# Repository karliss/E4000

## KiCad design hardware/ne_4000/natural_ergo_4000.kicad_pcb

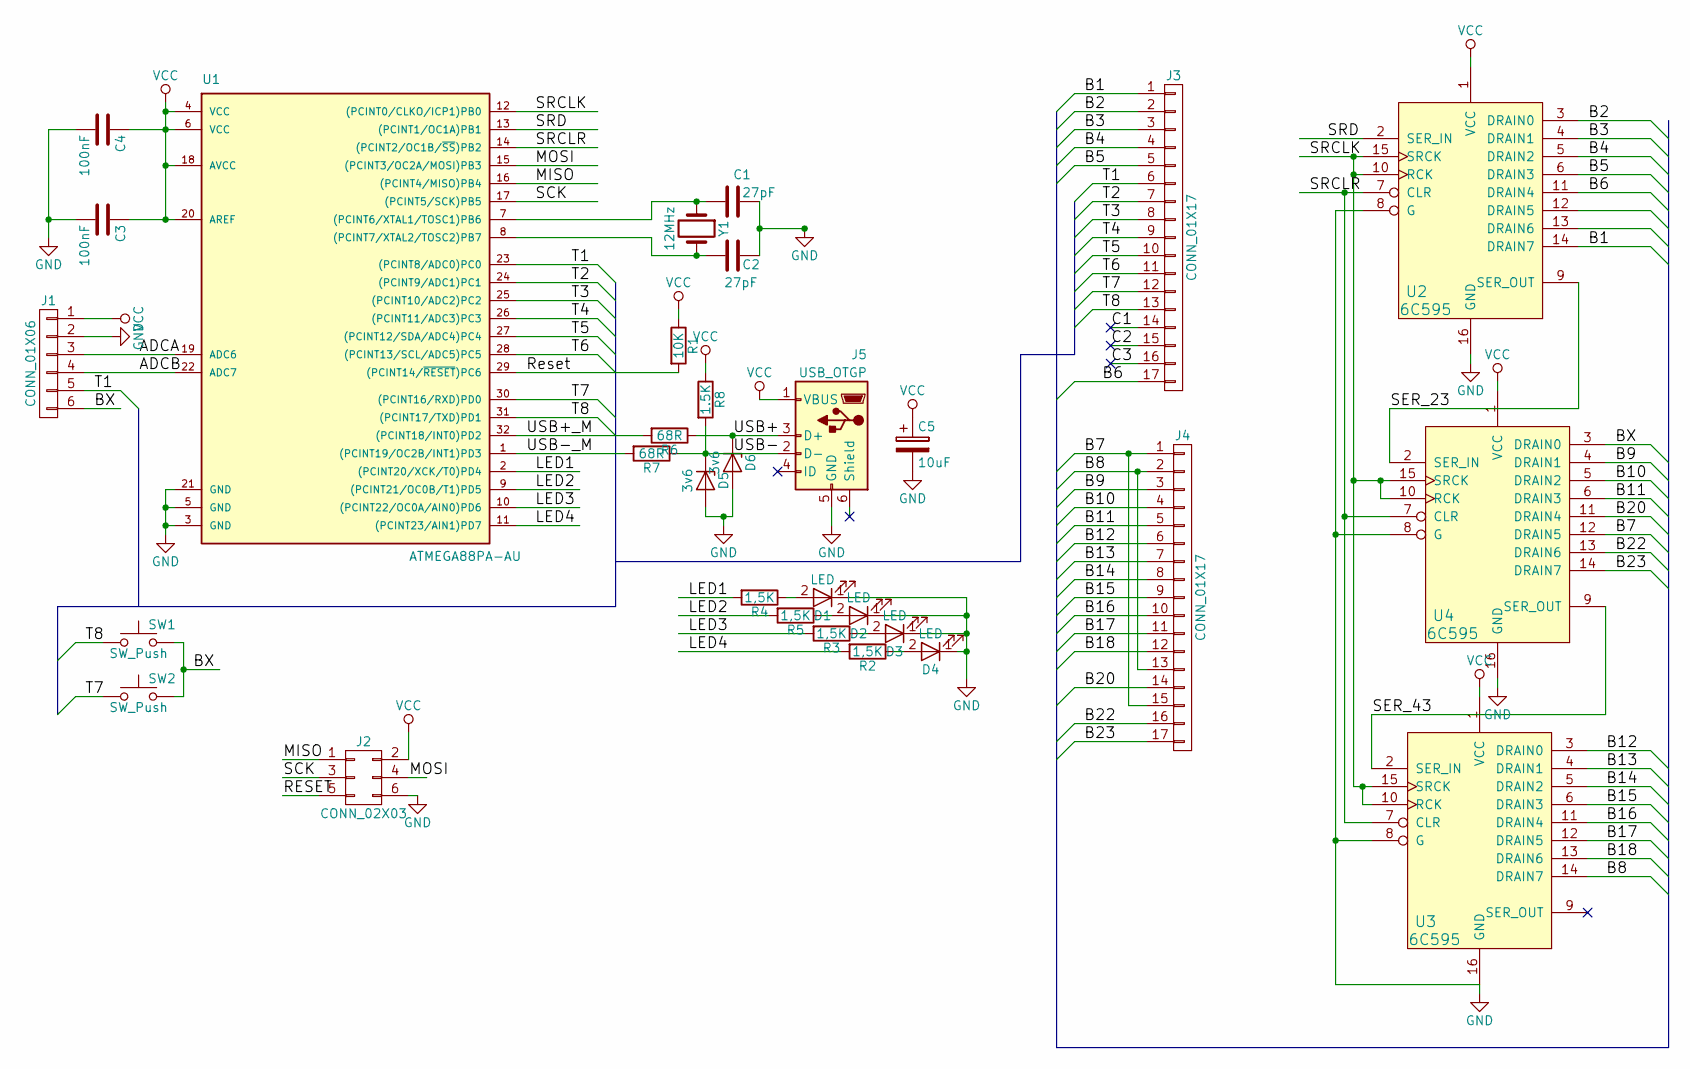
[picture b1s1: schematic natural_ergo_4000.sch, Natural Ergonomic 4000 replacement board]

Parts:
C1, C2: 27pF; C_Disc_D5.0mm_W2.5mm_P5.00mm
C3, C4: 100nF; C_0805
C5: 10uF; CP_Radial_D5.0mm_P2.50mm
D1, D2, D3, D4: LED; LED_D3.0mm
D5, D6: 3v6; D_DO-35_SOD27_P7.62mm_Horizontal
J1: CONN_01X06; Pin_Header_Straight_1x06_Pitch2.54mm
J2: CONN_02X03; Pin_Header_Straight_2x03_Pitch2.54mm
J3, J4: CONN_01X17; test_pad
J5: USB_OTGP; USB_Mini-B
R1: 10K; R_0805_HandSoldering
R2, R3, R4, R5: 1,5K; R_0805_HandSoldering
R6, R7: 68R; R_0805_HandSoldering
R8: 1.5K; R_0805_HandSoldering
SW1, SW2: SW_Push; SW_PUSH_6mm
U1: ATMEGA88PA-AU; LQFP-32_7x7mm_Pitch0.8mm
U2, U3, U4: 6C595; SOIC-16_3.9x9.9mm_Pitch1.27mm
Y1: 12MHz; Crystal_HC49-4H_Vertical

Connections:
/ADCA: J1.3, U1.19 (ADC6)
/ADCB: J1.4, U1.22 (ADC7)
/B1: J3.1, U2.14 (DRAIN7)
/B2: J3.2, U2.3 (DRAIN0)
/B3: J3.3, U2.4 (DRAIN1)
/B4: J3.4, U2.5 (DRAIN2)
/B5: J3.5, U2.6 (DRAIN3)
/B6: J3.17, U2.11 (DRAIN4)
/B7: J4.1, J4.15, U4.12 (DRAIN5)
/B8: J4.2, J4.13, U3.14 (DRAIN7)
/B9: J4.3, U4.4 (DRAIN1)
/B10: J4.4, U4.5 (DRAIN2)
/B11: J4.5, U4.6 (DRAIN3)
/B12: J4.6, U3.3 (DRAIN0)
/B13: J4.7, U3.4 (DRAIN1)
/B14: J4.8, U3.5 (DRAIN2)
/B15: J4.9, U3.6 (DRAIN3)
/B16: J4.10, U3.11 (DRAIN4)
/B17: J4.11, U3.12 (DRAIN5)
/B18: J4.12, U3.13 (DRAIN6)
/B20: J4.14, U4.11 (DRAIN4)
/B22: J4.16, U4.13 (DRAIN6)
/B23: J4.17, U4.14 (DRAIN7)
/BX: J1.6, SW1.2, SW2.2, U4.3 (DRAIN0)
/C1: J3.14
/C2: J3.15
/C3: J3.16
/LED1: R4.2, U1.2 ((PCINT20/XCK/T0)PD4)
/LED2: R5.2, U1.9 ((PCINT21/OC0B/T1)PD5)
/LED3: R3.2, U1.10 ((PCINT22/OC0A/AIN0)PD6)
/LED4: R2.2, U1.11 ((PCINT23/AIN1)PD7)
/MISO: J2.1, U1.16 ((PCINT4/MISO)PB4)
/MOSI: J2.4, U1.15 ((PCINT3/OC2A/MOSI)PB3)
/RESET: J2.5, R1.2, U1.29 ((PCINT14/~RESET~)PC6)
/SCK: J2.3, U1.17 ((PCINT5/SCK)PB5)
/SER_23: U2.9 (SER_OUT), U4.2 (SER_IN)
/SER_43: U3.2 (SER_IN), U4.9 (SER_OUT)
/SRCLK: U1.12 ((PCINT0/CLKO/ICP1)PB0), U2.10 (RCK), U2.15 (SRCK), U3.10 (RCK), U3.15 (SRCK), U4.10 (RCK), U4.15 (SRCK)
/SRCLR: U1.14 ((PCINT2/OC1B/~SS~)PB2), U2.7 (CLR), U3.7 (CLR), U4.7 (CLR)
/SRD: U1.13 ((PCINT1/OC1A)PB1), U2.2 (SER_IN)
/T1: J1.5, J3.6, U1.23 ((PCINT8/ADC0)PC0)
/T2: J3.7, U1.24 ((PCINT9/ADC1)PC1)
/T3: J3.8, U1.25 ((PCINT10/ADC2)PC2)
/T4: J3.9, U1.26 ((PCINT11/ADC3)PC3)
/T5: J3.10, U1.27 ((PCINT12/SDA/ADC4)PC4)
/T6: J3.11, U1.28 ((PCINT13/SCL/ADC5)PC5)
/T7: J3.12, SW2.1, U1.30 ((PCINT16/RXD)PD0)
/T8: J3.13, SW1.1, U1.31 ((PCINT17/TXD)PD1)
/USB+: D6.1 (K), J5.3 (D+), R6.1
/USB+_M: R6.2, U1.32 ((PCINT18/INT0)PD2)
/USB-: D5.1 (K), J5.2 (D-), R7.1, R8.2
/USB-_M: R7.2, U1.1 ((PCINT19/OC2B/INT1)PD3)
GND: C1.1, C2.1, C3.2, C4.2, C5.2, D1.1 (K), D2.1 (K), D3.1 (K), D4.1 (K), D5.2 (A), D6.2 (A), J1.2, J2.6, J5.5 (GND), U1.3 (GND), U1.5 (GND), U1.21 (GND), U2.8 (G), U2.16 (GND), U3.8 (G), U3.16 (GND), U4.8 (G), U4.16 (GND)
unnamed: C1.2, U1.7 ((PCINT6/XTAL1/TOSC1)PB6), Y1.1
unnamed: C2.2, U1.8 ((PCINT7/XTAL2/TOSC2)PB7), Y1.2
unnamed: D1.2 (A), R4.1
unnamed: D2.2 (A), R5.1
unnamed: D3.2 (A), R3.1
unnamed: D4.2 (A), R2.1
VCC: C3.1, C4.1, C5.1, J1.1, J2.2, J5.1 (VBUS), R1.1, R8.1, U1.4 (VCC), U1.6 (VCC), U1.18 (AVCC), U1.20 (AREF), U2.1 (VCC), U3.1 (VCC), U4.1 (VCC)

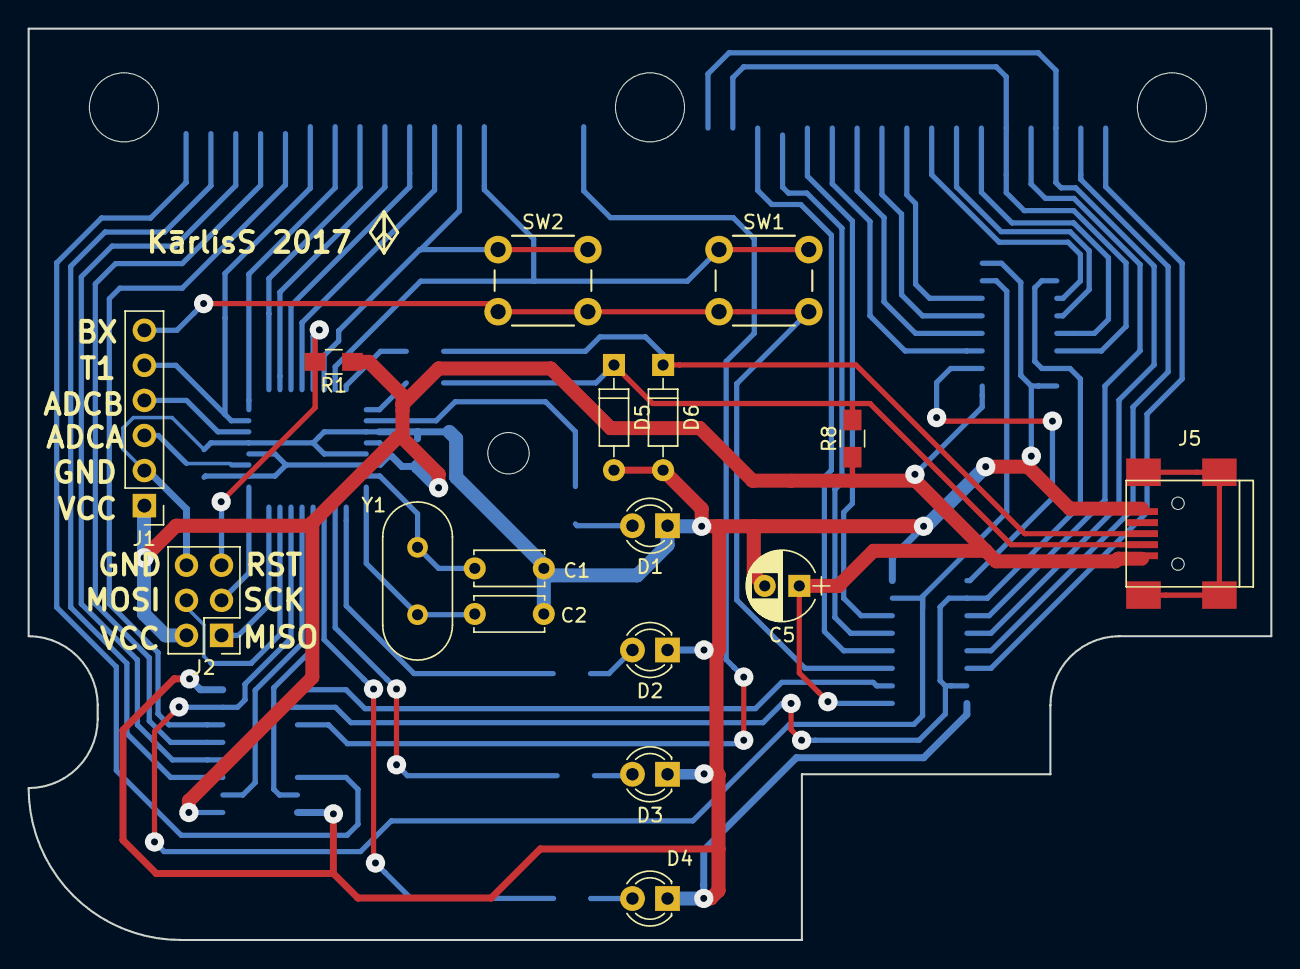
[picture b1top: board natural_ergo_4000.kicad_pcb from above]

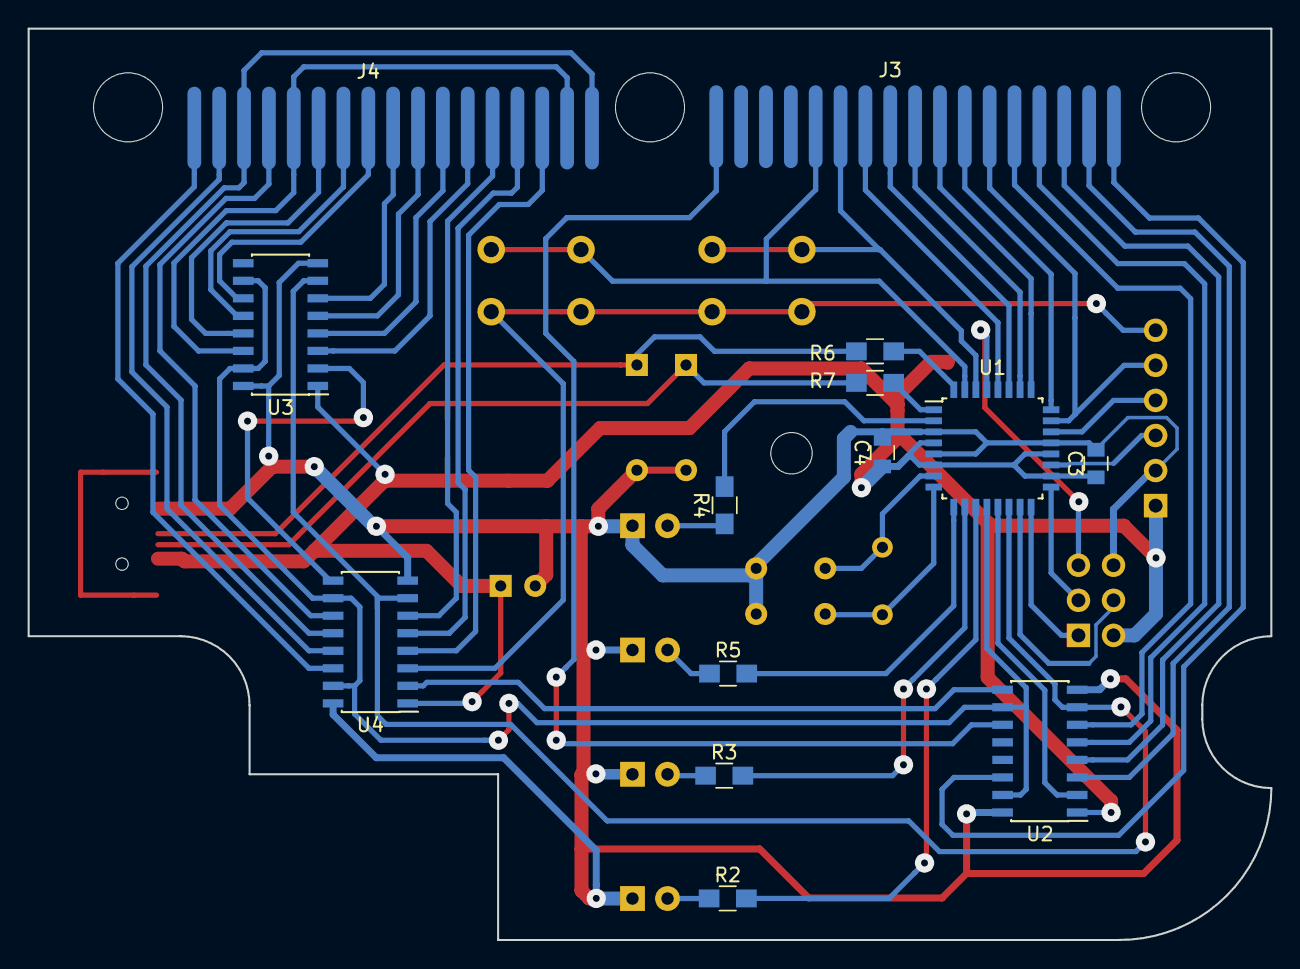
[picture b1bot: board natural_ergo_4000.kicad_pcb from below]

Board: 2 copper layers, 90.0 x 66.0 mm, 31 parts (14 on the bottom side), 57 nets.

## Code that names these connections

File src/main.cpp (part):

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    return ~result;
}

const uint8_t SRCLK = (1 << PB0);
const uint8_t SRD = (1 << PB1);
const uint8_t SRCLR = (1 << PB2);

const uint8_t SHIFTR_MASK = SRCLK | SRCLR | SRD;

static void initHardware()
{
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    PORTC |= 0x3f; // rows pullups
    
    // ROW7 ROW8, LED1 LED2 LED3 LED4
    DDRD = (0 << PD0) | (0 << PD1) | (1 << PD4) | (1 << PD5) | (1 << PD6) | (1 << PD7);
    PORTD = 0x3;
    
    DDRB = SHIFTR_MASK;
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
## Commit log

2017-06-04 Added pcb schematics.
2017-06-04 Add v-usb as submodule
2017-06-05 Minimal keyboard configuration.
2017-06-18 Matrix scan test code.
2017-07-30 Replace shift registers with open drain version.
2017-09-06 Adjust PCB layout spacing
    * increase spacing around middle screw
    * move R8 to allow vertical cappacitor mounting
    * add more labels
2020-02-27 Last commit in AVR branch with unknown set of changes.
2020-02-27 Last commit 2
2020-02-27 Third attempt at saving kicad files.
